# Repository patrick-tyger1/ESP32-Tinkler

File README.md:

# ESP32-Tinkler
EAGLE Files for Tinkler

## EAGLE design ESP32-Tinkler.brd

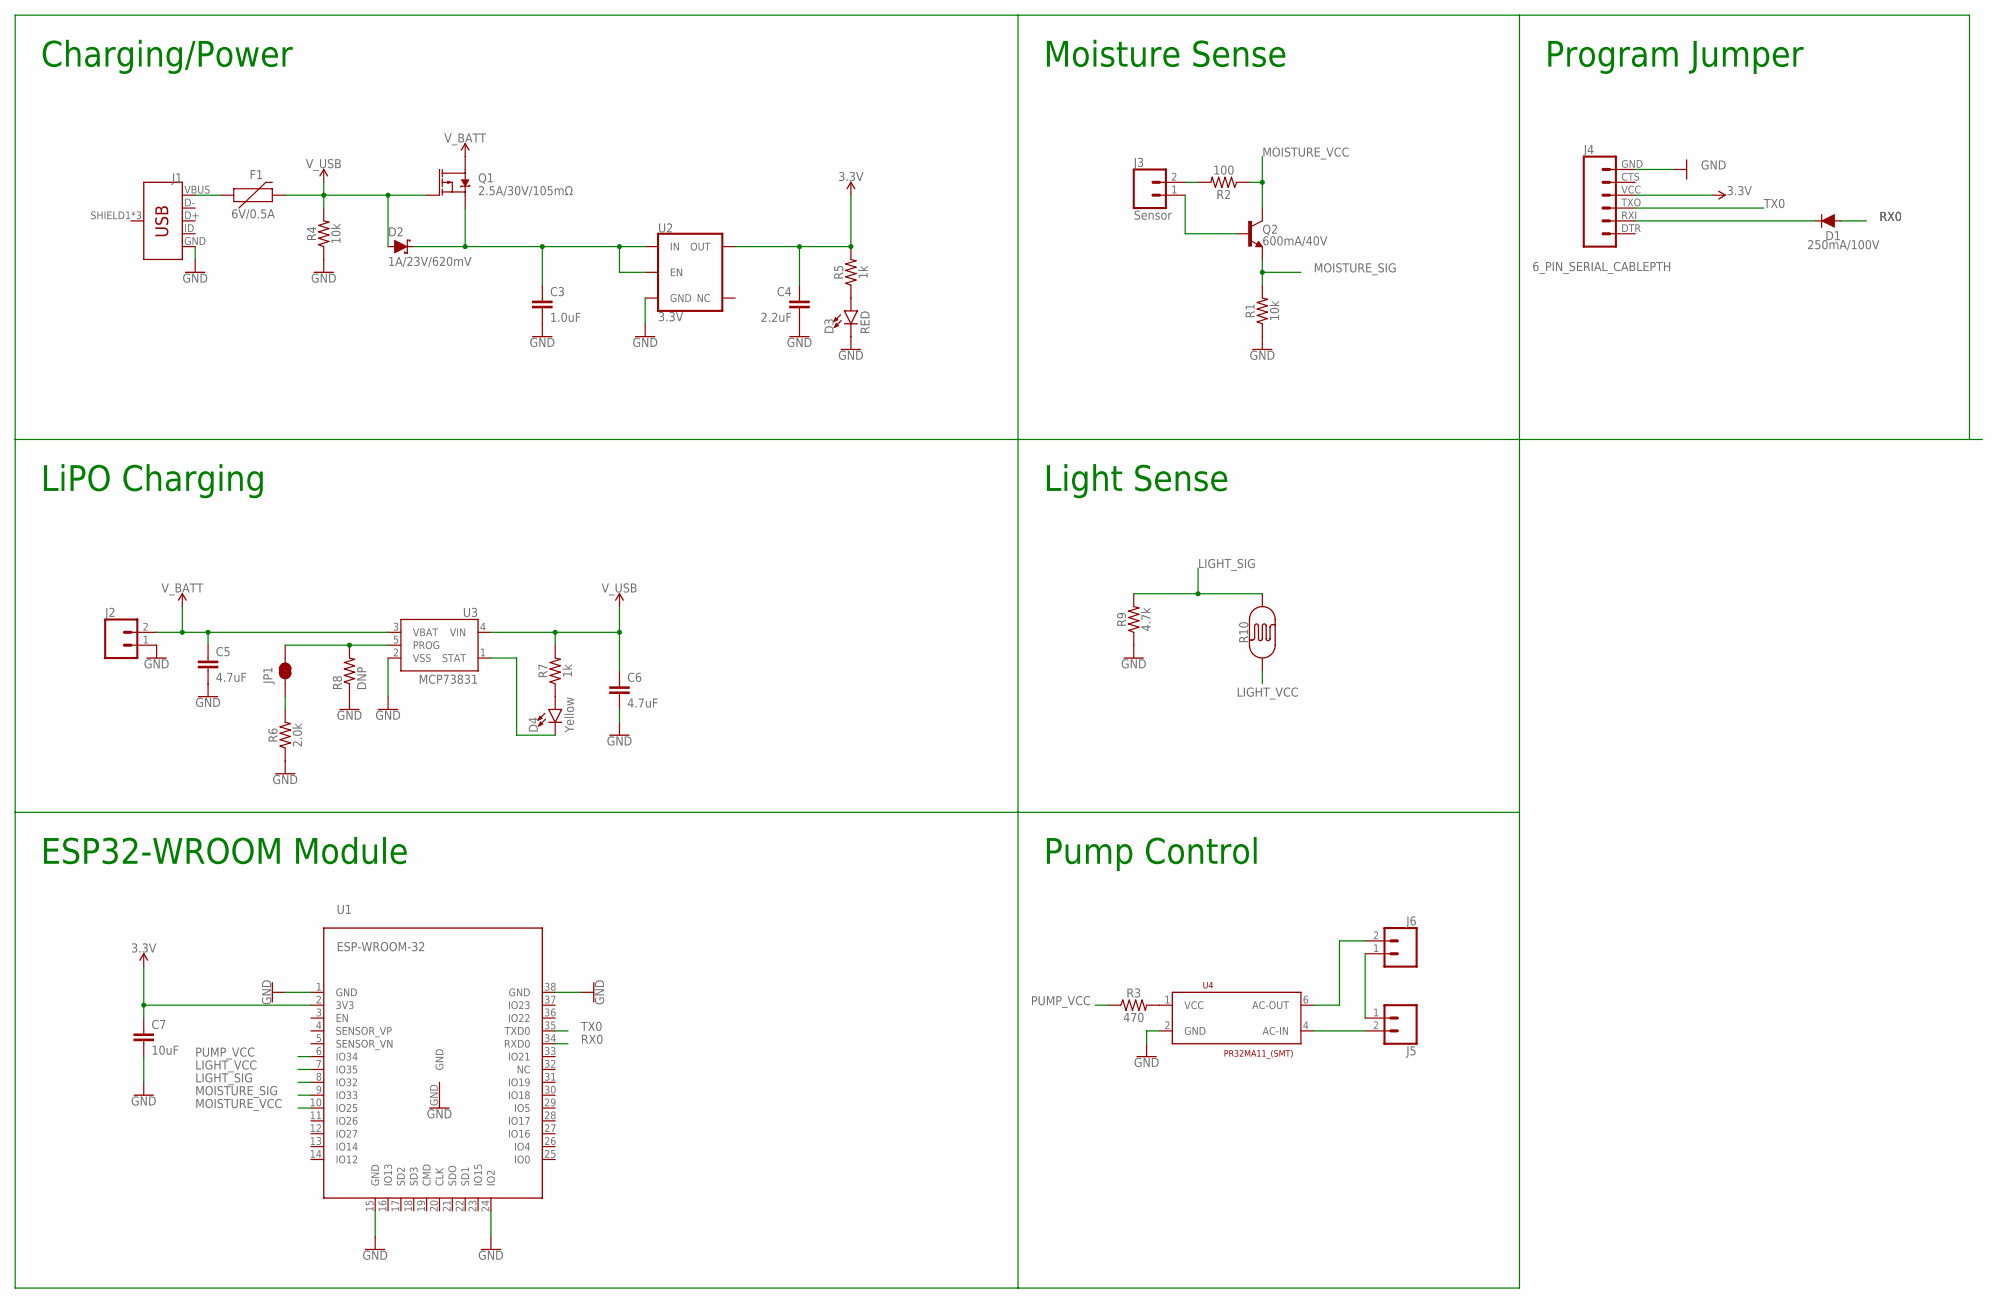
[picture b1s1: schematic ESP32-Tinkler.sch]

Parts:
C3: 1.0uF; 0603
C4: 2.2uF; 0603
C5, C6: 4.7uF; 0603
C7: 10uF; 0603
D1: 250mA/100V; SOD-323
D2: 1A/23V/620mV; SOD-323
D3: RED; LED-0603
D4: Yellow; LED-0603
F1: 6V/0.5A; 1206
J1: USB_MICRO-B_FEMALE-SMT; USB-B-MICRO-SMD
J2: CONN_02JST-PTH-2; JST-2-PTH
J3: Sensor; JST-2-PTH
J4: 6_PIN_SERIAL_CABLEPTH; FTDI_BASIC
J5, J6: CONN_02PTH4; 1X02_XTRA_BIG
JP1: JUMPER-SMT_2_NC_TRACE_SILK; SMT-JUMPER_2_NC_TRACE_SILK
Q1: 2.5A/30V/105mΩ; SOT23-3
Q2: 600mA/40V; SOT23-3
R1, R4: 10k; 0603
R2: 100; 0603
R3: 470; 0603
R5, R7: 1k; 0603
R6: 2.0k; 0603
R8: DNP; 0603-RES
R9: 4.7k; 0603
R10: PHOTOCELLPTH-KIT; PHOTOCELL-KIT
U1: ESP-WROOM-32
U2: 3.3V; SOT23-5
U3: MCP73831; SOT23-5
U4: PR32MA11_(SMT); SMT-GULLWING

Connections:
3.3V: C4.1, C7.1, J4.VCC (4), R5.2, U1.2 (3V3), U2.5 (OUT)
GND: C3.2, C4.2, C5.2, C6.2, C7.2, D3.C, J1.GND, J2.1, J4.GND (6), R1.1, R4.1, R6.1, R8.1, R9.1, U1.1 (GND), U1.15 (GND), U1.24 (IO2), U1.38 (GND), U1.GND, U2.2 (GND), U3.2 (VSS), U4.2 (GND)
LIGHT_SIG: R9.2, R10.2, U1.8 (IO32)
LIGHT_VCC: R10.1, U1.7 (IO35)
MOISTURE_SIG: Q2.2 (E), R1.2, U1.9 (IO33)
MOISTURE_VCC: Q2.3 (C), R2.1, U1.10 (IO25)
unnamed: J3.2, R2.2
unnamed: F1.1, J1.VBUS
unnamed: C3.1, D2.C, Q1.2 (S), U2.1 (IN), U2.3 (EN)
unnamed: J3.1, Q2.1 (B)
unnamed: D1.C, J4.RXI (2)
unnamed: JP1.2, R8.2, U3.5 (PROG)
unnamed: D3.A, R5.1
unnamed: D4.A, R7.1
unnamed: JP1.1, R6.2
unnamed: J5.1, J6.1
unnamed: D4.C, U3.1 (STAT)
unnamed: J6.2, U4.6 (AC-OUT)
unnamed: J5.2, U4.4 (AC-IN)
unnamed: R3.2, U4.1 (VCC)
PUMP_VCC: R3.1, U1.6 (IO34)
RX0: D1.A, U1.34 (RXD0)
TX0: J4.TXO (3), U1.35 (TXD0)
V_BATT: C5.1, J2.2, Q1.3 (D), U3.3 (VBAT)
V_USB: C6.1, D2.A, F1.2, Q1.1 (G), R4.2, R7.2, U3.4 (VIN)

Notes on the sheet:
Charging/Power
LiPO Charging
Moisture Sense
ESP32-WROOM Module
Light Sense
Pump Control
Program Jumper

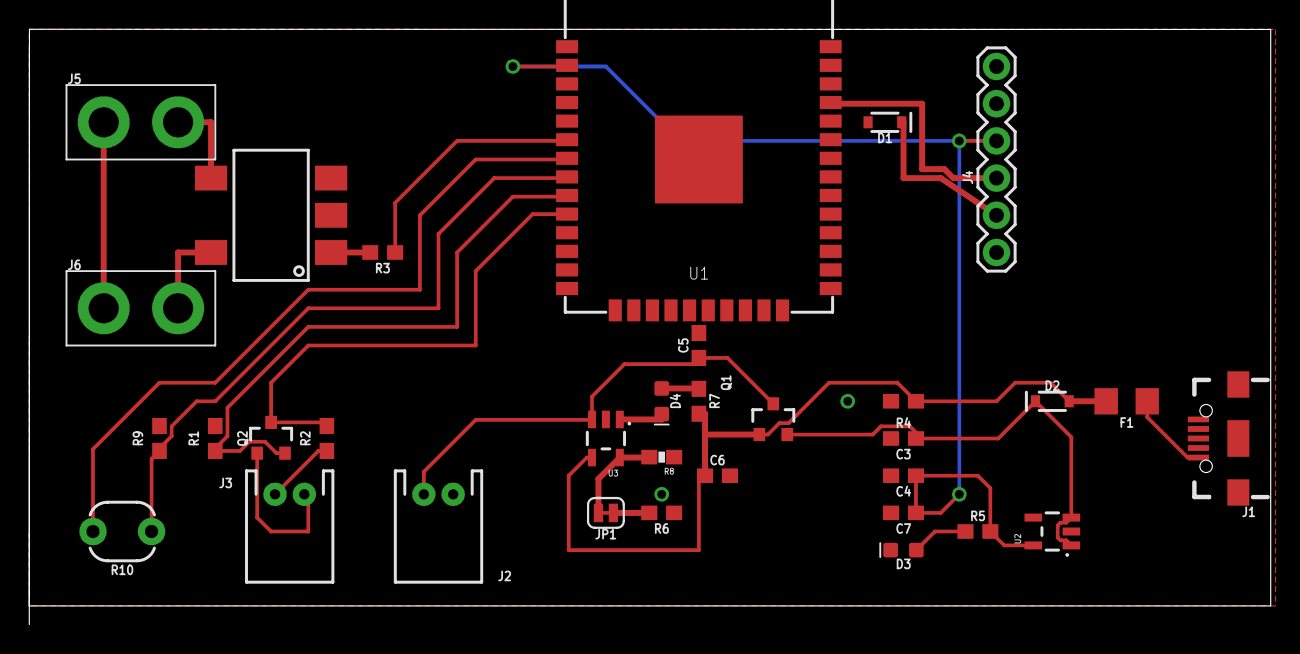
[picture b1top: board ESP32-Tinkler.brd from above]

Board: 2 copper layers, 84.8 x 40.6 mm, 33 parts (0 on the bottom side), 25 nets.

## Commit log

2017-07-08 removed unnecessary files

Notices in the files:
parts and their libraries:
SparkFun-Capacitors: Licensing: Creative Commons ShareAlike 4.0 International - https://creativecommons.org/licenses/by-sa/4.0
SparkFun-Passives: Licensing: CC v3.0 Share-Alike You are welcome to use this library for commercial purposes.
